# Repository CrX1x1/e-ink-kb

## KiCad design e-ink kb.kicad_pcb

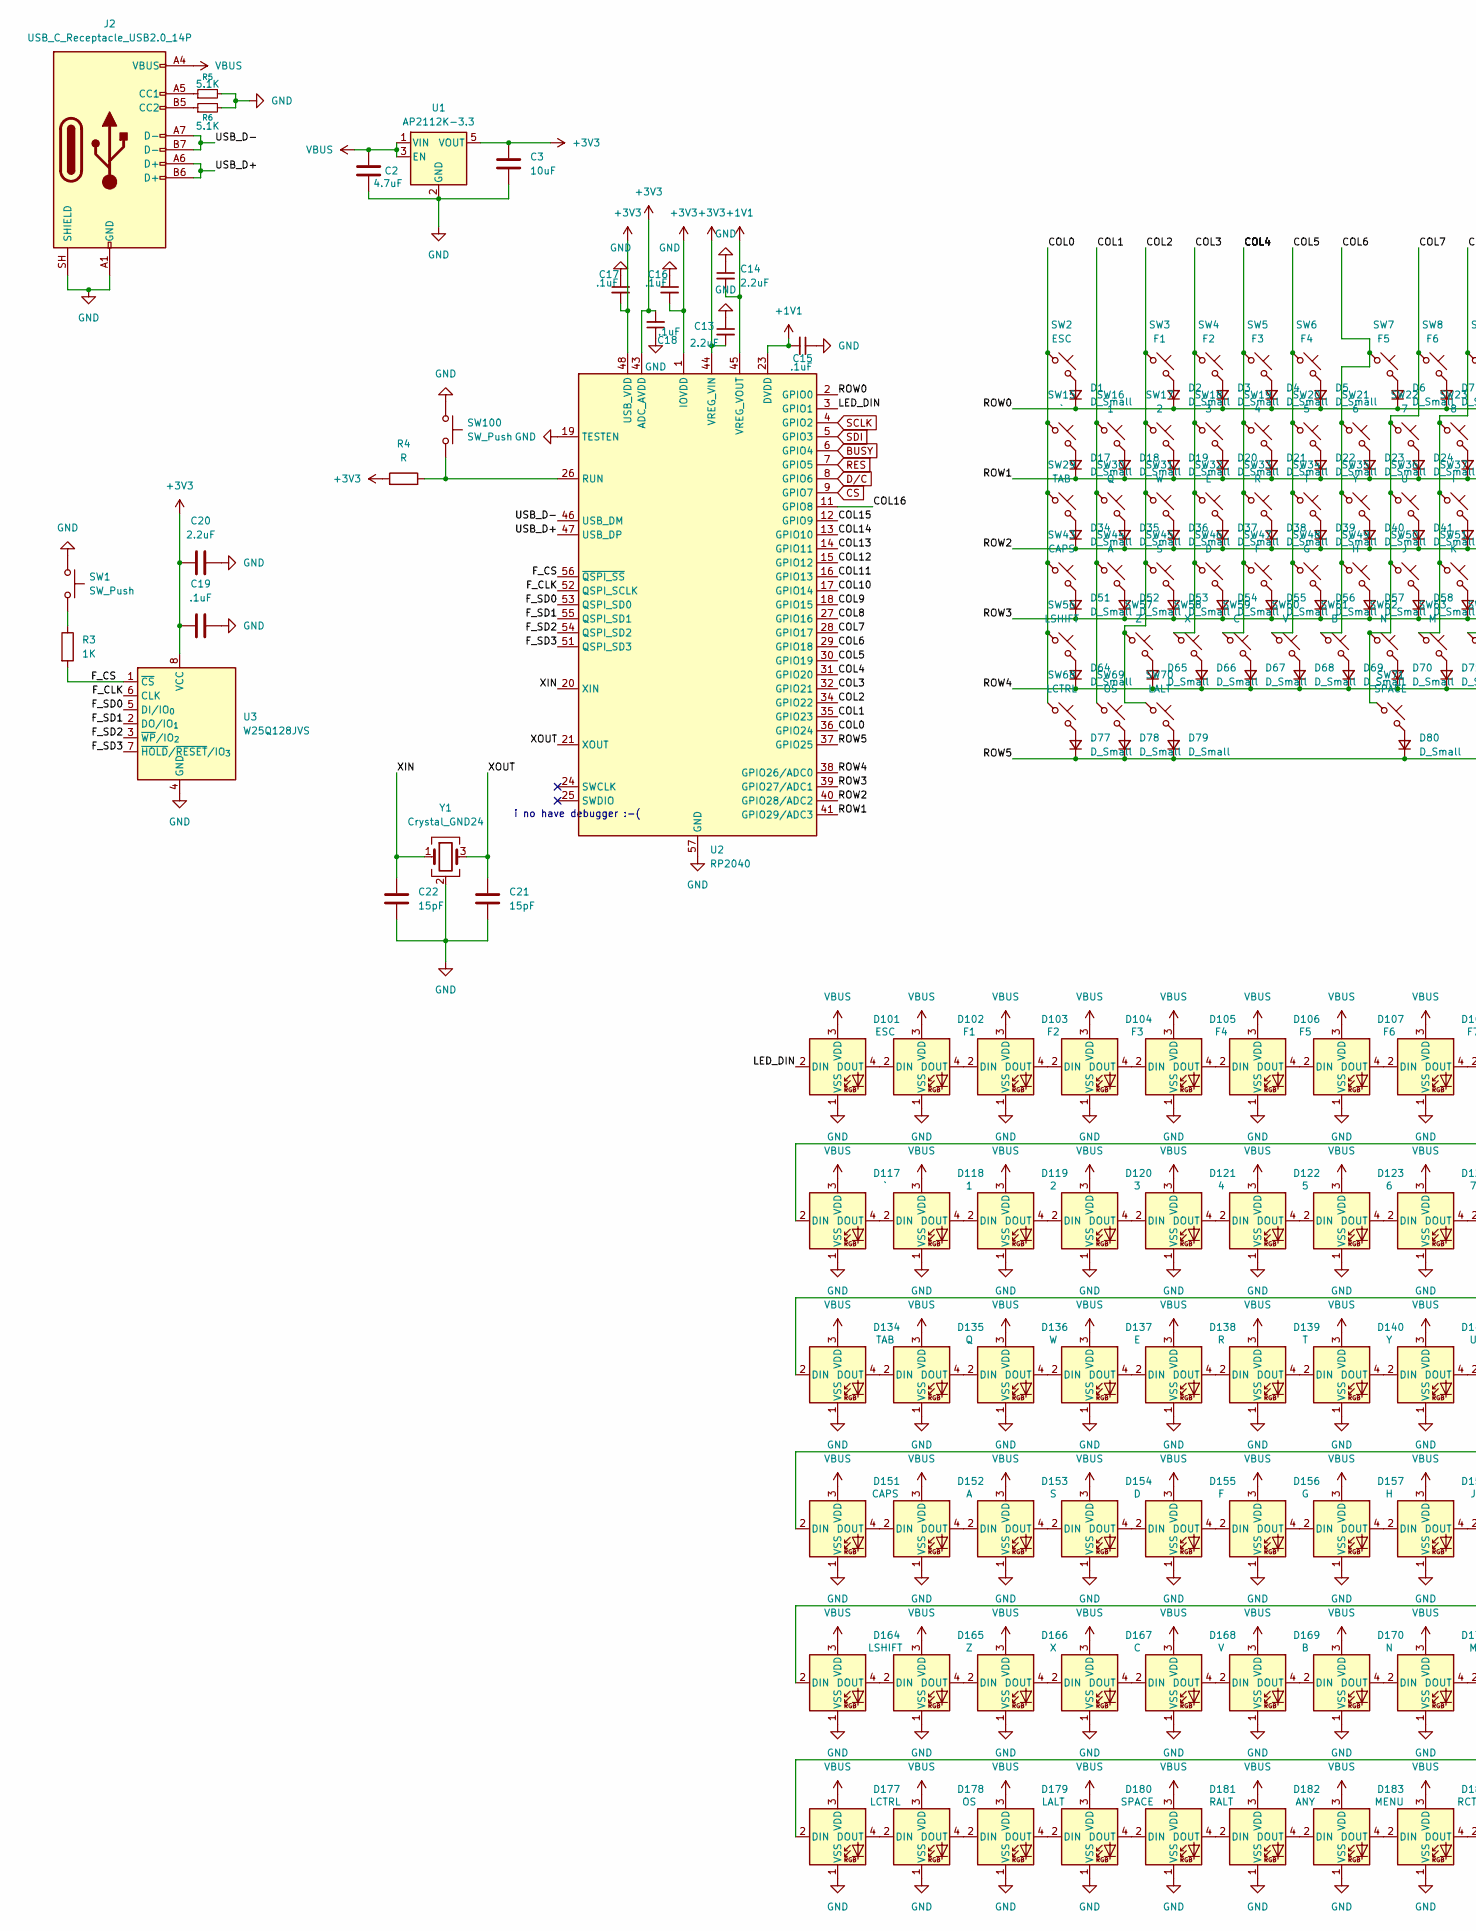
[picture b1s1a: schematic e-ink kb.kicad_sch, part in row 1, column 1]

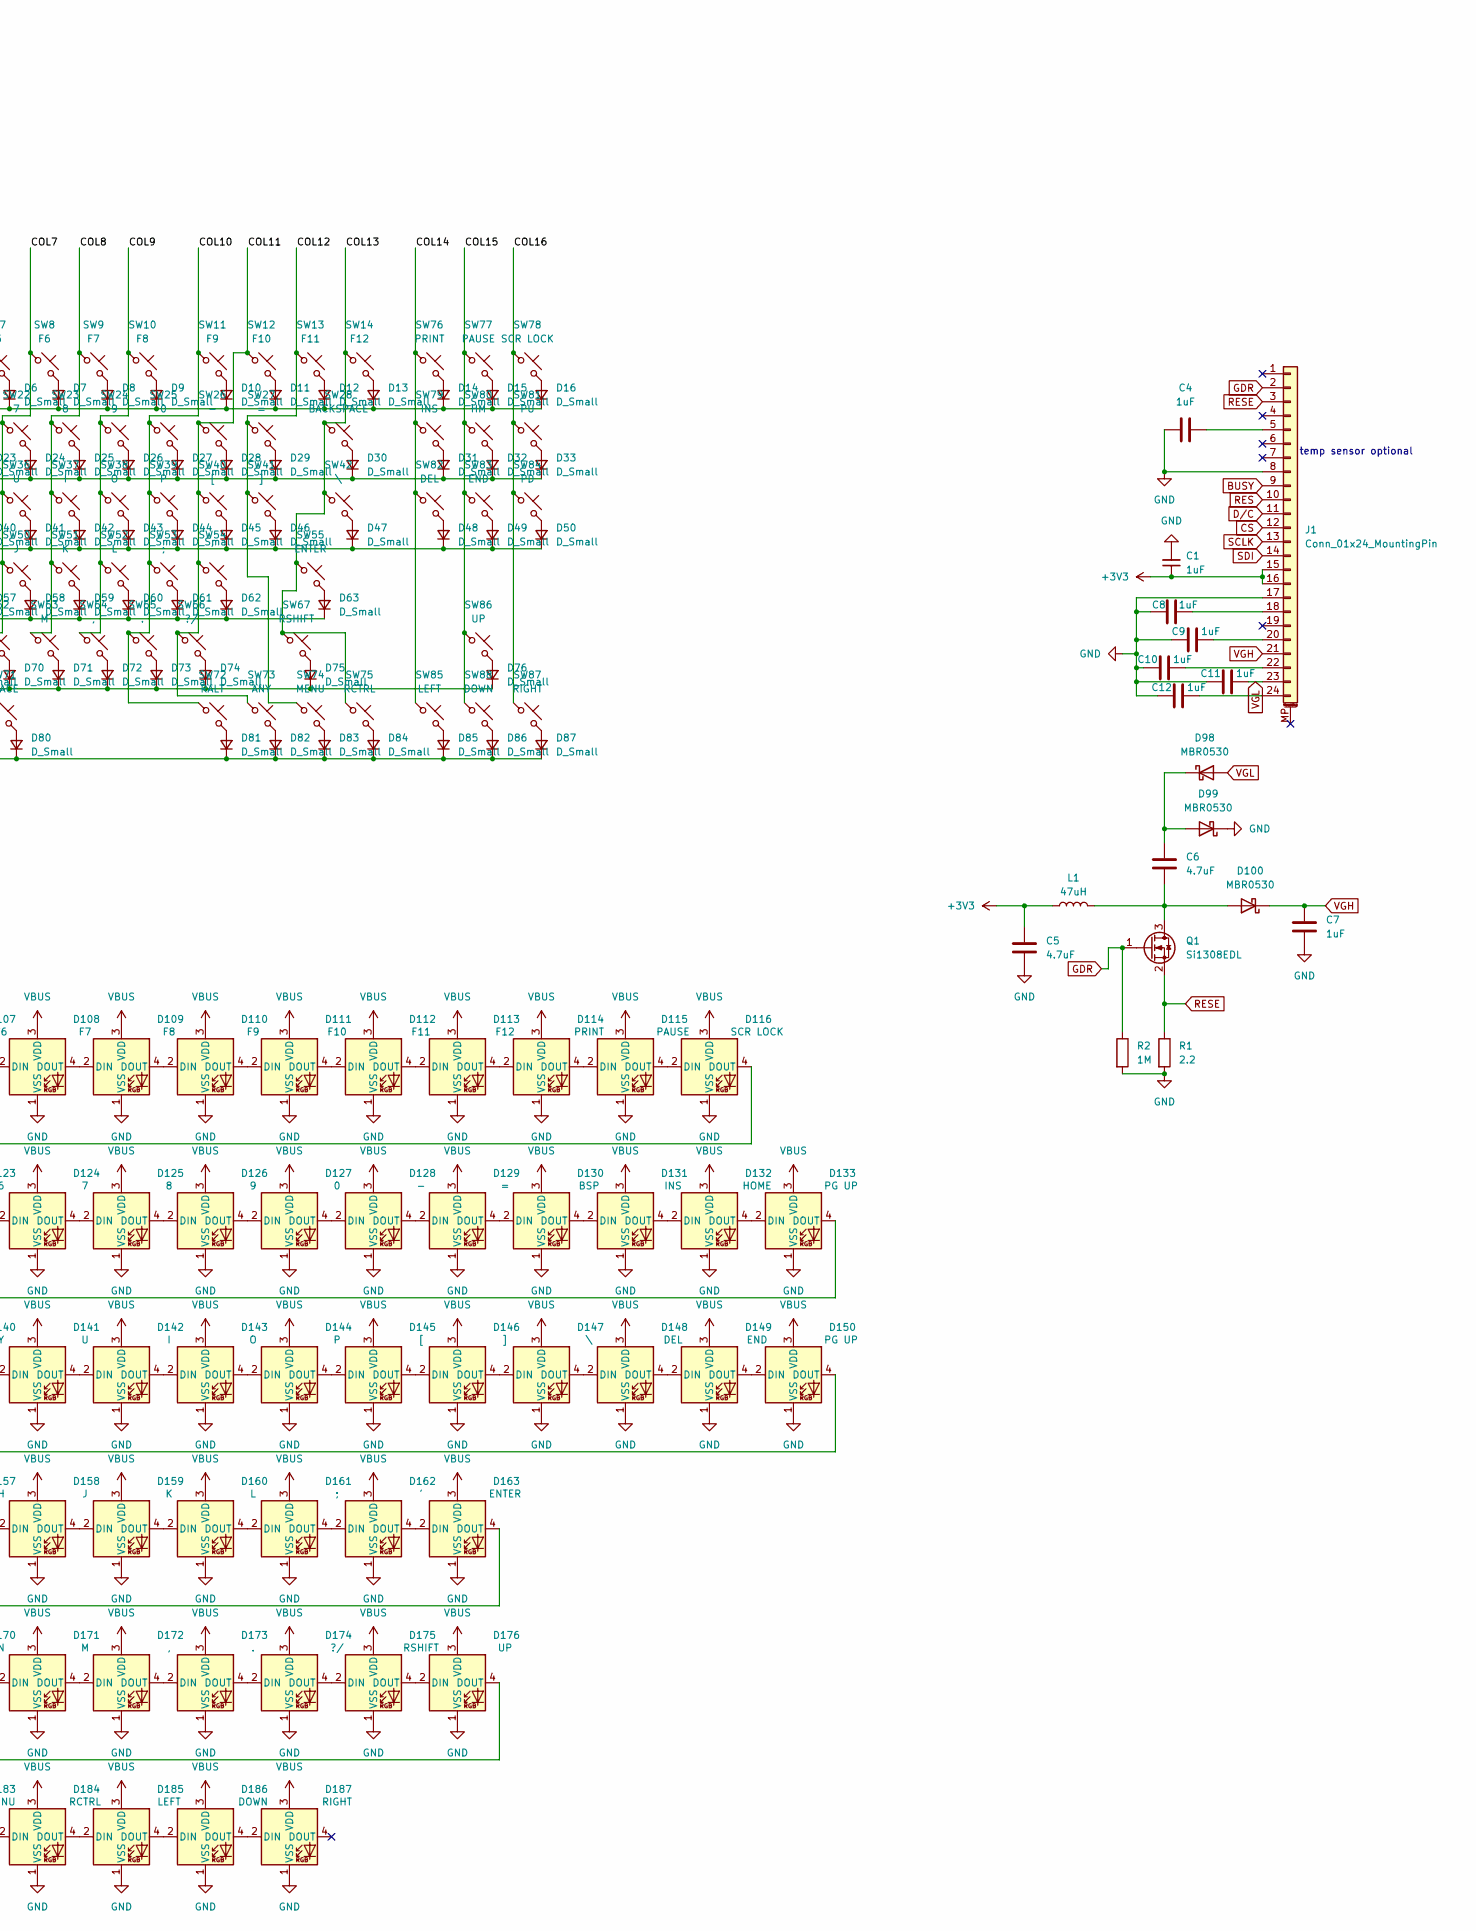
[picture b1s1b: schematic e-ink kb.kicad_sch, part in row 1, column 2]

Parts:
C1, C4, C7, C8, C9, C10, C11, C12: 1uF; C_0805_2012Metric_Pad1.18x1.45mm_HandSolder
C2, C5, C6: 4.7uF; C_0805_2012Metric_Pad1.18x1.45mm_HandSolder
C3: 10uF; C_0805_2012Metric_Pad1.18x1.45mm_HandSolder
C13, C14, C20: 2.2uF; C_0805_2012Metric_Pad1.18x1.45mm_HandSolder
C15, C16, C17, C18, C19: .1uF; C_0805_2012Metric_Pad1.18x1.45mm_HandSolder
C21, C22: 15pF; C_0805_2012Metric_Pad1.18x1.45mm_HandSolder
D1, D2, D3, D4, D5, D6, D7, D8, D9, D10, D11, D12, D13, D14, D15, D16, D17, D18, D19, D20, D21, D22, D23, D24, D25, D26, D27, D28, D29, D30, D31, D32, D33, D34, D35, D36, D37, D38, D39, D40, D41, D42, D43, D44, D45, D46, D47, D48, D49, D50, D51, D52, D53, D54, D55, D56, D57, D58, D59, D60, D61, D62, D63, D64, D65, D66, D67, D68, D69, D70, D71, D72, D73, D74, D75, D76, D77, D78, D79, D80, D81, D82, D83, D84, D85, D86, D87: D_Small; D_SOD-323F
D98, D99, D100: MBR0530; D_SOD-123
D101: ESC; LED_SK6812MINI-E_3.2x2.8mm_P1.5mm_ReverseMount
D102: F1; LED_SK6812MINI-E_3.2x2.8mm_P1.5mm_ReverseMount
D103: F2; LED_SK6812MINI-E_3.2x2.8mm_P1.5mm_ReverseMount
D104: F3; LED_SK6812MINI-E_3.2x2.8mm_P1.5mm_ReverseMount
D105: F4; LED_SK6812MINI-E_3.2x2.8mm_P1.5mm_ReverseMount
D106: F5; LED_SK6812MINI-E_3.2x2.8mm_P1.5mm_ReverseMount
D107: F6; LED_SK6812MINI-E_3.2x2.8mm_P1.5mm_ReverseMount
D108: F7; LED_SK6812MINI-E_3.2x2.8mm_P1.5mm_ReverseMount
D109: F8; LED_SK6812MINI-E_3.2x2.8mm_P1.5mm_ReverseMount
D110: F9; LED_SK6812MINI-E_3.2x2.8mm_P1.5mm_ReverseMount
D111: F10; LED_SK6812MINI-E_3.2x2.8mm_P1.5mm_ReverseMount
D112: F11; LED_SK6812MINI-E_3.2x2.8mm_P1.5mm_ReverseMount
D113: F12; LED_SK6812MINI-E_3.2x2.8mm_P1.5mm_ReverseMount
D114: PRINT; LED_SK6812MINI-E_3.2x2.8mm_P1.5mm_ReverseMount
D115: PAUSE; LED_SK6812MINI-E_3.2x2.8mm_P1.5mm_ReverseMount
D116: SCR LOCK; LED_SK6812MINI-E_3.2x2.8mm_P1.5mm_ReverseMount
D117: `; LED_SK6812MINI-E_3.2x2.8mm_P1.5mm_ReverseMount
D118: 1; LED_SK6812MINI-E_3.2x2.8mm_P1.5mm_ReverseMount
D119: 2; LED_SK6812MINI-E_3.2x2.8mm_P1.5mm_ReverseMount
D120: 3; LED_SK6812MINI-E_3.2x2.8mm_P1.5mm_ReverseMount
D121: 4; LED_SK6812MINI-E_3.2x2.8mm_P1.5mm_ReverseMount
D122: 5; LED_SK6812MINI-E_3.2x2.8mm_P1.5mm_ReverseMount
D123: 6; LED_SK6812MINI-E_3.2x2.8mm_P1.5mm_ReverseMount
D124: 7; LED_SK6812MINI-E_3.2x2.8mm_P1.5mm_ReverseMount
D125: 8; LED_SK6812MINI-E_3.2x2.8mm_P1.5mm_ReverseMount
D126: 9; LED_SK6812MINI-E_3.2x2.8mm_P1.5mm_ReverseMount
D127: 0; LED_SK6812MINI-E_3.2x2.8mm_P1.5mm_ReverseMount
D128: -; LED_SK6812MINI-E_3.2x2.8mm_P1.5mm_ReverseMount
D129: =; LED_SK6812MINI-E_3.2x2.8mm_P1.5mm_ReverseMount
D130: BSP; LED_SK6812MINI-E_3.2x2.8mm_P1.5mm_ReverseMount
D131: INS; LED_SK6812MINI-E_3.2x2.8mm_P1.5mm_ReverseMount
D132: HOME; LED_SK6812MINI-E_3.2x2.8mm_P1.5mm_ReverseMount
D133, D150: PG UP; LED_SK6812MINI-E_3.2x2.8mm_P1.5mm_ReverseMount
D134: TAB; LED_SK6812MINI-E_3.2x2.8mm_P1.5mm_ReverseMount
D135: Q; LED_SK6812MINI-E_3.2x2.8mm_P1.5mm_ReverseMount
D136: W; LED_SK6812MINI-E_3.2x2.8mm_P1.5mm_ReverseMount
D137: E; LED_SK6812MINI-E_3.2x2.8mm_P1.5mm_ReverseMount
D138: R; LED_SK6812MINI-E_3.2x2.8mm_P1.5mm_ReverseMount
D139: T; LED_SK6812MINI-E_3.2x2.8mm_P1.5mm_ReverseMount
D140: Y; LED_SK6812MINI-E_3.2x2.8mm_P1.5mm_ReverseMount
D141: U; LED_SK6812MINI-E_3.2x2.8mm_P1.5mm_ReverseMount
D142: I; LED_SK6812MINI-E_3.2x2.8mm_P1.5mm_ReverseMount
D143: O; LED_SK6812MINI-E_3.2x2.8mm_P1.5mm_ReverseMount
D144: P; LED_SK6812MINI-E_3.2x2.8mm_P1.5mm_ReverseMount
D145: [; LED_SK6812MINI-E_3.2x2.8mm_P1.5mm_ReverseMount
D146: ]; LED_SK6812MINI-E_3.2x2.8mm_P1.5mm_ReverseMount
D147: \; LED_SK6812MINI-E_3.2x2.8mm_P1.5mm_ReverseMount
D148: DEL; LED_SK6812MINI-E_3.2x2.8mm_P1.5mm_ReverseMount
D149: END; LED_SK6812MINI-E_3.2x2.8mm_P1.5mm_ReverseMount
D151: CAPS; LED_SK6812MINI-E_3.2x2.8mm_P1.5mm_ReverseMount
D152: A; LED_SK6812MINI-E_3.2x2.8mm_P1.5mm_ReverseMount
D153: S; LED_SK6812MINI-E_3.2x2.8mm_P1.5mm_ReverseMount
D154: D; LED_SK6812MINI-E_3.2x2.8mm_P1.5mm_ReverseMount
D155: F; LED_SK6812MINI-E_3.2x2.8mm_P1.5mm_ReverseMount
D156: G; LED_SK6812MINI-E_3.2x2.8mm_P1.5mm_ReverseMount
D157: H; LED_SK6812MINI-E_3.2x2.8mm_P1.5mm_ReverseMount
D158: J; LED_SK6812MINI-E_3.2x2.8mm_P1.5mm_ReverseMount
D159: K; LED_SK6812MINI-E_3.2x2.8mm_P1.5mm_ReverseMount
D160: L; LED_SK6812MINI-E_3.2x2.8mm_P1.5mm_ReverseMount
D161: ;; LED_SK6812MINI-E_3.2x2.8mm_P1.5mm_ReverseMount
D162: '; LED_SK6812MINI-E_3.2x2.8mm_P1.5mm_ReverseMount
D163: ENTER; LED_SK6812MINI-E_3.2x2.8mm_P1.5mm_ReverseMount
D164: LSHIFT; LED_SK6812MINI-E_3.2x2.8mm_P1.5mm_ReverseMount
D165: Z; LED_SK6812MINI-E_3.2x2.8mm_P1.5mm_ReverseMount
D166: X; LED_SK6812MINI-E_3.2x2.8mm_P1.5mm_ReverseMount
D167: C; LED_SK6812MINI-E_3.2x2.8mm_P1.5mm_ReverseMount
D168: V; LED_SK6812MINI-E_3.2x2.8mm_P1.5mm_ReverseMount
D169: B; LED_SK6812MINI-E_3.2x2.8mm_P1.5mm_ReverseMount
D170: N; LED_SK6812MINI-E_3.2x2.8mm_P1.5mm_ReverseMount
D171: M; LED_SK6812MINI-E_3.2x2.8mm_P1.5mm_ReverseMount
D172: ,; LED_SK6812MINI-E_3.2x2.8mm_P1.5mm_ReverseMount
D173: .; LED_SK6812MINI-E_3.2x2.8mm_P1.5mm_ReverseMount
D174: ?/; LED_SK6812MINI-E_3.2x2.8mm_P1.5mm_ReverseMount
D175: RSHIFT; LED_SK6812MINI-E_3.2x2.8mm_P1.5mm_ReverseMount
D176: UP; LED_SK6812MINI-E_3.2x2.8mm_P1.5mm_ReverseMount
D177: LCTRL; LED_SK6812MINI-E_3.2x2.8mm_P1.5mm_ReverseMount
D178: OS; LED_SK6812MINI-E_3.2x2.8mm_P1.5mm_ReverseMount
D179: LALT; LED_SK6812MINI-E_3.2x2.8mm_P1.5mm_ReverseMount
D180: SPACE; LED_SK6812MINI-E_3.2x2.8mm_P1.5mm_ReverseMount
D181: RALT; LED_SK6812MINI-E_3.2x2.8mm_P1.5mm_ReverseMount
D182: ANY; LED_SK6812MINI-E_3.2x2.8mm_P1.5mm_ReverseMount
D183: MENU; LED_SK6812MINI-E_3.2x2.8mm_P1.5mm_ReverseMount
D184: RCTRL; LED_SK6812MINI-E_3.2x2.8mm_P1.5mm_ReverseMount
D185: LEFT; LED_SK6812MINI-E_3.2x2.8mm_P1.5mm_ReverseMount
D186: DOWN; LED_SK6812MINI-E_3.2x2.8mm_P1.5mm_ReverseMount
D187: RIGHT; LED_SK6812MINI-E_3.2x2.8mm_P1.5mm_ReverseMount
J1: Conn_01x24_MountingPin; Molex_502231-2400_1x24-1SH_P0.5mm_Vertical
J2: USB_C_Receptacle_USB2.0_14P; USB_C_Receptacle_Amphenol_12401948E412A
L1: 47uH; L_APV_ANR3015
Q1: Si1308EDL; SOT-323_SC-70
R1: 2.2; R_0805_2012Metric_Pad1.20x1.40mm_HandSolder
R2: 1M; R_0805_2012Metric_Pad1.20x1.40mm_HandSolder
R3: 1K; R_0805_2012Metric_Pad1.20x1.40mm_HandSolder
R4: R; R_0805_2012Metric_Pad1.20x1.40mm_HandSolder
R5, R6: 5.1K; R_0805_2012Metric_Pad1.20x1.40mm_HandSolder
SW1, SW100: SW_Push; SW_Push_SPST_NO_Alps_SKRK
SW2: ESC; SW_Cherry_MX_1.00u_PCB
SW3: F1; SW_Cherry_MX_1.00u_PCB
SW4: F2; SW_Cherry_MX_1.00u_PCB
SW5: F3; SW_Cherry_MX_1.00u_PCB
SW6: F4; SW_Cherry_MX_1.00u_PCB
SW7: F5; SW_Cherry_MX_1.00u_PCB
SW8: F6; SW_Cherry_MX_1.00u_PCB
SW9: F7; SW_Cherry_MX_1.00u_PCB
SW10: F8; SW_Cherry_MX_1.00u_PCB
SW11: F9; SW_Cherry_MX_1.00u_PCB
SW12: F10; SW_Cherry_MX_1.00u_PCB
SW13: F11; SW_Cherry_MX_1.00u_PCB
SW14: F12; SW_Cherry_MX_1.00u_PCB
SW15: `; SW_Cherry_MX_1.00u_PCB
SW16: 1; SW_Cherry_MX_1.00u_PCB
SW17: 2; SW_Cherry_MX_1.00u_PCB
SW18: 3; SW_Cherry_MX_1.00u_PCB
SW19: 4; SW_Cherry_MX_1.00u_PCB
SW20: 5; SW_Cherry_MX_1.00u_PCB
SW21: 6; SW_Cherry_MX_1.00u_PCB
SW22: 7; SW_Cherry_MX_1.00u_PCB
SW23: 8; SW_Cherry_MX_1.00u_PCB
SW24: 9; SW_Cherry_MX_1.00u_PCB
SW25: 0; SW_Cherry_MX_1.00u_PCB
SW26: -; SW_Cherry_MX_1.00u_PCB
SW27: =; SW_Cherry_MX_1.00u_PCB
SW28: BACKSPACE; SW_Cherry_MX_2.00u_PCB
SW29: TAB; SW_Cherry_MX_1.50u_PCB
SW30: Q; SW_Cherry_MX_1.00u_PCB
SW31: W; SW_Cherry_MX_1.00u_PCB
SW32: E; SW_Cherry_MX_1.00u_PCB
SW33: R; SW_Cherry_MX_1.00u_PCB
SW34: T; SW_Cherry_MX_1.00u_PCB
SW35: Y; SW_Cherry_MX_1.00u_PCB
SW36: U; SW_Cherry_MX_1.00u_PCB
SW37: I; SW_Cherry_MX_1.00u_PCB
SW38: O; SW_Cherry_MX_1.00u_PCB
SW39: P; SW_Cherry_MX_1.00u_PCB
SW40: [; SW_Cherry_MX_1.00u_PCB
SW41: ]; SW_Cherry_MX_1.00u_PCB
SW42: \; SW_Cherry_MX_1.50u_PCB
SW43: CAPS; SW_Cherry_MX_1.75u_PCB
SW44: A; SW_Cherry_MX_1.00u_PCB
SW45: S; SW_Cherry_MX_1.00u_PCB
SW46: D; SW_Cherry_MX_1.00u_PCB
SW47: F; SW_Cherry_MX_1.00u_PCB
SW48: G; SW_Cherry_MX_1.00u_PCB
SW49: H; SW_Cherry_MX_1.00u_PCB
SW50: J; SW_Cherry_MX_1.00u_PCB
SW51: K; SW_Cherry_MX_1.00u_PCB
SW52: L; SW_Cherry_MX_1.00u_PCB
SW53: ;; SW_Cherry_MX_1.00u_PCB
SW54: '; SW_Cherry_MX_1.00u_PCB
SW55: ENTER; SW_Cherry_MX_2.25u_PCB
SW56: LSHIFT; SW_Cherry_MX_2.25u_PCB
SW57: Z; SW_Cherry_MX_1.00u_PCB
SW58: X; SW_Cherry_MX_1.00u_PCB
SW59: C; SW_Cherry_MX_1.00u_PCB
SW60: V; SW_Cherry_MX_1.00u_PCB
SW61: B; SW_Cherry_MX_1.00u_PCB
SW62: N; SW_Cherry_MX_1.00u_PCB
SW63: M; SW_Cherry_MX_1.00u_PCB
SW64: ,; SW_Cherry_MX_1.00u_PCB
SW65: .; SW_Cherry_MX_1.00u_PCB
SW66: ?/; SW_Cherry_MX_1.00u_PCB
SW67: RSHIFT; SW_Cherry_MX_2.75u_PCB
SW68: LCTRL; SW_Cherry_MX_1.25u_PCB
SW69: OS; SW_Cherry_MX_1.25u_PCB
SW70: LALT; SW_Cherry_MX_1.25u_PCB
SW71: SPACE; SW_Cherry_MX_6.25u_PCB
SW72: RALT; SW_Cherry_MX_1.25u_PCB
SW73: ANY; SW_Cherry_MX_1.25u_PCB
SW74: MENU; SW_Cherry_MX_1.25u_PCB
SW75: RCTRL; SW_Cherry_MX_1.25u_PCB
SW76: PRINT; SW_Cherry_MX_1.00u_PCB
SW77: PAUSE; SW_Cherry_MX_1.00u_PCB
SW78: SCR LOCK; SW_Cherry_MX_1.00u_PCB
SW79: INS; SW_Cherry_MX_1.00u_PCB
SW80: HM; SW_Cherry_MX_1.00u_PCB
SW81: PU; SW_Cherry_MX_1.00u_PCB
SW82: DEL; SW_Cherry_MX_1.00u_PCB
SW83: END; SW_Cherry_MX_1.00u_PCB
SW84: PD; SW_Cherry_MX_1.00u_PCB
SW85: LEFT; SW_Cherry_MX_1.00u_PCB
SW86: UP; SW_Cherry_MX_1.00u_PCB
SW87: RIGHT; SW_Cherry_MX_1.00u_PCB
SW88: DOWN; SW_Cherry_MX_1.00u_PCB
U1: AP2112K-3.3; SOT-23-5
U2: RP2040; QFN-56-1EP_7x7mm_P0.4mm_EP3.2x3.2mm
U3: W25Q128JVS; SOIC-8_5.3x5.3mm_P1.27mm
Y1: Crystal_GND24; Crystal_SMD_3225-4Pin_3.2x2.5mm_HandSoldering

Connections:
+1V1: C14.2, C15.2, U2.23 (DVDD), U2.45 (VREG_VOUT), U2.50 (DVDD)
+3V3: C1.1, C3.1, C5.1, C13.2, C16.2, C17.2, C18.2, C19.2, C20.2, J1.15, J1.16, L1.1, R4.1, U1.5 (VOUT), U2.1 (IOVDD), U2.10 (IOVDD), U2.22 (IOVDD), U2.33 (IOVDD), U2.42 (IOVDD), U2.43 (ADC_AVDD), U2.44 (VREG_VIN), U2.48 (USB_VDD), U2.49 (IOVDD), U3.8 (VCC)
/COL0: SW2.1, SW15.1, SW29.1, SW43.1, SW56.1, SW68.1, U2.36 (GPIO24)
/COL1: SW16.1, SW30.1, SW44.1, SW69.1, U2.35 (GPIO23)
/COL2: SW3.1, SW17.1, SW31.1, SW45.1, SW57.1, SW70.1, U2.34 (GPIO22)
/COL3: SW4.1, SW18.1, SW32.1, SW46.1, SW58.1, U2.32 (GPIO21)
/COL4: SW5.1, SW19.1, SW33.1, SW47.1, SW59.1, U2.31 (GPIO20)
/COL5: SW6.1, SW20.1, SW34.1, SW48.1, SW60.1, U2.30 (GPIO19)
/COL6: SW7.1, SW21.1, SW35.1, SW49.1, SW61.1, U2.29 (GPIO18)
/COL7: SW8.1, SW22.1, SW36.1, SW50.1, SW62.1, SW71.1, U2.28 (GPIO17)
/COL8: SW9.1, SW23.1, SW37.1, SW51.1, SW63.1, U2.27 (GPIO16)
/COL9: SW10.1, SW24.1, SW38.1, SW52.1, SW64.1, U2.18 (GPIO15)
/COL10: SW11.1, SW25.1, SW39.1, SW53.1, SW65.1, SW72.1, U2.17 (GPIO14)
/COL11: SW12.1, SW26.1, SW40.1, SW54.1, SW66.1, SW73.1, U2.16 (GPIO13)
/COL12: SW13.1, SW27.1, SW41.1, SW74.1, U2.15 (GPIO12)
/COL13: SW14.1, SW28.1, SW42.1, SW55.1, SW67.1, SW75.1, U2.14 (GPIO11)
/COL14: SW76.1, SW79.1, SW82.1, SW85.1, U2.13 (GPIO10)
/COL15: SW77.1, SW80.1, SW83.1, SW86.1, SW88.1, U2.12 (GPIO9)
/COL16: SW78.1, SW81.1, SW84.1, SW87.1, U2.11 (GPIO8)
/F_CLK: U2.52 (QSPI_SCLK), U3.6 (CLK)
/F_CS: R3.2, U2.56 (~QSPI_SS), U3.1 (~CS)
/F_SD0: U2.53 (QSPI_SD0), U3.5 (DI/IO_{0})
/F_SD1: U2.55 (QSPI_SD1), U3.2 (DO/IO_{1})
/F_SD2: U2.54 (QSPI_SD2), U3.3 (~WP/IO_{2})
/F_SD3: U2.51 (QSPI_SD3), U3.7 (~HOLD/~RESET/IO_{3})
/LED_DIN: D101.2 (DIN), U2.3 (GPIO1)
/ROW0: D1.1 (K), D2.1 (K), D3.1 (K), D4.1 (K), D5.1 (K), D6.1 (K), D7.1 (K), D8.1 (K), D9.1 (K), D10.1 (K), D11.1 (K), D12.1 (K), D13.1 (K), D14.1 (K), D15.1 (K), D16.1 (K), U2.2 (GPIO0)
/ROW1: D17.1 (K), D18.1 (K), D19.1 (K), D20.1 (K), D21.1 (K), D22.1 (K), D23.1 (K), D24.1 (K), D25.1 (K), D26.1 (K), D27.1 (K), D28.1 (K), D29.1 (K), D30.1 (K), D31.1 (K), D32.1 (K), D33.1 (K), U2.41 (GPIO29/ADC3)
/ROW2: D34.1 (K), D35.1 (K), D36.1 (K), D37.1 (K), D38.1 (K), D39.1 (K), D40.1 (K), D41.1 (K), D42.1 (K), D43.1 (K), D44.1 (K), D45.1 (K), D46.1 (K), D47.1 (K), D48.1 (K), D49.1 (K), D50.1 (K), U2.40 (GPIO28/ADC2)
/ROW3: D51.1 (K), D52.1 (K), D53.1 (K), D54.1 (K), D55.1 (K), D56.1 (K), D57.1 (K), D58.1 (K), D59.1 (K), D60.1 (K), D61.1 (K), D62.1 (K), D63.1 (K), U2.39 (GPIO27/ADC1)
/ROW4: D64.1 (K), D65.1 (K), D66.1 (K), D67.1 (K), D68.1 (K), D69.1 (K), D70.1 (K), D71.1 (K), D72.1 (K), D73.1 (K), D74.1 (K), D75.1 (K), D76.1 (K), U2.38 (GPIO26/ADC0)
/ROW5: D77.1 (K), D78.1 (K), D79.1 (K), D80.1 (K), D81.1 (K), D82.1 (K), D83.1 (K), D84.1 (K), D85.1 (K), D86.1 (K), D87.1 (K), U2.37 (GPIO25)
/USB_D+: J2.A6 (D+), J2.B6 (D+), U2.47 (USB_DP)
/USB_D-: J2.A7 (D-), J2.B7 (D-), U2.46 (USB_DM)
/XIN: C22.1, U2.20 (XIN), Y1.1
/XOUT: C21.1, U2.21 (XOUT), Y1.3
BUSY: J1.9, U2.6 (GPIO4)
CS: J1.12, U2.9 (GPIO7)
D/C: J1.11, U2.8 (GPIO6)
GDR: J1.2, Q1.1 (G), R2.1
GND: C1.2, C2.2, C3.2, C4.1, C5.2, C7.2, C8.1, C9.1, C10.1, C11.1, C12.1, C13.1, C14.1, C15.1, C16.1, C17.1, C18.1, C19.1, C20.1, C21.2, C22.2, D99.1 (K), D101.1 (VSS), D102.1 (VSS), D103.1 (VSS), D104.1 (VSS), D105.1 (VSS), D106.1 (VSS), D107.1 (VSS), D108.1 (VSS), D109.1 (VSS), D110.1 (VSS), D111.1 (VSS), D112.1 (VSS), D113.1 (VSS), D114.1 (VSS), D115.1 (VSS), D116.1 (VSS), D117.1 (VSS), D118.1 (VSS), D119.1 (VSS), D120.1 (VSS), D121.1 (VSS), D122.1 (VSS), D123.1 (VSS), D124.1 (VSS), D125.1 (VSS), D126.1 (VSS), D127.1 (VSS), D128.1 (VSS), D129.1 (VSS), D130.1 (VSS), D131.1 (VSS), D132.1 (VSS), D133.1 (VSS), D134.1 (VSS), D135.1 (VSS), D136.1 (VSS), D137.1 (VSS), D138.1 (VSS), D139.1 (VSS), D140.1 (VSS), D141.1 (VSS), D142.1 (VSS), D143.1 (VSS), D144.1 (VSS), D145.1 (VSS), D146.1 (VSS), D147.1 (VSS), D148.1 (VSS), D149.1 (VSS), D150.1 (VSS), D151.1 (VSS), D152.1 (VSS), D153.1 (VSS), D154.1 (VSS), D155.1 (VSS), D156.1 (VSS), D157.1 (VSS), D158.1 (VSS), D159.1 (VSS), D160.1 (VSS), D161.1 (VSS), D162.1 (VSS), D163.1 (VSS), D164.1 (VSS), D165.1 (VSS), D166.1 (VSS), D167.1 (VSS), D168.1 (VSS), D169.1 (VSS), D170.1 (VSS), D171.1 (VSS), D172.1 (VSS), D173.1 (VSS), D174.1 (VSS), D175.1 (VSS), D176.1 (VSS), D177.1 (VSS), D178.1 (VSS), D179.1 (VSS), D180.1 (VSS), D181.1 (VSS), D182.1 (VSS), D183.1 (VSS), D184.1 (VSS), D185.1 (VSS), D186.1 (VSS), D187.1 (VSS), J1.8, J1.17, J2.A1 (GND), J2.A12 (GND), J2.B1 (GND), J2.B12 (GND), J2.SH (SHIELD), R1.2, R2.2, R5.2, R6.2, SW1.1, SW100.1, U1.2 (GND), U2.19 (TESTEN), U2.57 (GND), U3.4 (GND), Y1.2 (G), Y1.4 (G)
unnamed: D1.2 (A), SW2.2
unnamed: D2.2 (A), SW3.2
unnamed: D3.2 (A), SW4.2
unnamed: D4.2 (A), SW5.2
unnamed: D5.2 (A), SW6.2
unnamed: D6.2 (A), SW7.2
unnamed: D7.2 (A), SW8.2
unnamed: D8.2 (A), SW9.2
unnamed: D9.2 (A), SW10.2
unnamed: D10.2 (A), SW11.2
unnamed: D11.2 (A), SW12.2
unnamed: D12.2 (A), SW13.2
unnamed: D13.2 (A), SW14.2
unnamed: D14.2 (A), SW76.2
unnamed: D15.2 (A), SW77.2
unnamed: D16.2 (A), SW78.2
unnamed: D17.2 (A), SW15.2
unnamed: D18.2 (A), SW16.2
unnamed: D19.2 (A), SW17.2
unnamed: D20.2 (A), SW18.2
unnamed: D21.2 (A), SW19.2
unnamed: D22.2 (A), SW20.2
unnamed: D23.2 (A), SW21.2
unnamed: D24.2 (A), SW22.2
unnamed: D25.2 (A), SW23.2
unnamed: D26.2 (A), SW24.2
unnamed: D27.2 (A), SW25.2
unnamed: D28.2 (A), SW26.2
unnamed: D29.2 (A), SW27.2
unnamed: D30.2 (A), SW28.2
unnamed: D31.2 (A), SW79.2
unnamed: D32.2 (A), SW80.2
unnamed: D33.2 (A), SW81.2
unnamed: D34.2 (A), SW29.2
unnamed: D35.2 (A), SW30.2
unnamed: D36.2 (A), SW31.2
unnamed: D37.2 (A), SW32.2
unnamed: D38.2 (A), SW33.2
unnamed: D39.2 (A), SW34.2
unnamed: D40.2 (A), SW35.2
unnamed: D41.2 (A), SW36.2
unnamed: D42.2 (A), SW37.2
unnamed: D43.2 (A), SW38.2
unnamed: D44.2 (A), SW39.2
unnamed: D45.2 (A), SW40.2
unnamed: D46.2 (A), SW41.2
unnamed: D47.2 (A), SW42.2
unnamed: D48.2 (A), SW82.2
unnamed: D49.2 (A), SW83.2
unnamed: D50.2 (A), SW84.2
unnamed: D51.2 (A), SW43.2
unnamed: D52.2 (A), SW44.2
unnamed: D53.2 (A), SW45.2
unnamed: D54.2 (A), SW46.2
unnamed: D55.2 (A), SW47.2
unnamed: D56.2 (A), SW48.2
unnamed: D57.2 (A), SW49.2
unnamed: D58.2 (A), SW50.2
unnamed: D59.2 (A), SW51.2
unnamed: D60.2 (A), SW52.2
unnamed: D61.2 (A), SW53.2
unnamed: D62.2 (A), SW54.2
unnamed: D63.2 (A), SW55.2
unnamed: D64.2 (A), SW56.2
unnamed: D65.2 (A), SW57.2
unnamed: D66.2 (A), SW58.2
unnamed: D67.2 (A), SW59.2
unnamed: D68.2 (A), SW60.2
unnamed: D69.2 (A), SW61.2
unnamed: D70.2 (A), SW62.2
unnamed: D71.2 (A), SW63.2
unnamed: D72.2 (A), SW64.2
unnamed: D73.2 (A), SW65.2
unnamed: D74.2 (A), SW66.2
unnamed: D75.2 (A), SW67.2
unnamed: D76.2 (A), SW86.2
unnamed: D77.2 (A), SW68.2
unnamed: D78.2 (A), SW69.2
unnamed: D79.2 (A), SW70.2
unnamed: D80.2 (A), SW71.2
unnamed: D81.2 (A), SW72.2
unnamed: D82.2 (A), SW73.2
unnamed: D83.2 (A), SW74.2
unnamed: D84.2 (A), SW75.2
unnamed: D85.2 (A), SW85.2
unnamed: D86.2 (A), SW88.2
unnamed: D87.2 (A), SW87.2
unnamed: C6.1, D98.1 (K), D99.2 (A)
unnamed: C6.2, D100.2 (A), L1.2, Q1.3 (D)
unnamed: D101.4 (DOUT), D102.2 (DIN)
unnamed: D102.4 (DOUT), D103.2 (DIN)
unnamed: D103.4 (DOUT), D104.2 (DIN)
unnamed: D104.4 (DOUT), D105.2 (DIN)
unnamed: D105.4 (DOUT), D106.2 (DIN)
unnamed: D106.4 (DOUT), D107.2 (DIN)
unnamed: D107.4 (DOUT), D108.2 (DIN)
unnamed: D108.4 (DOUT), D109.2 (DIN)
unnamed: D109.4 (DOUT), D110.2 (DIN)
unnamed: D110.4 (DOUT), D111.2 (DIN)
unnamed: D111.4 (DOUT), D112.2 (DIN)
unnamed: D112.4 (DOUT), D113.2 (DIN)
unnamed: D113.4 (DOUT), D114.2 (DIN)
unnamed: D114.4 (DOUT), D115.2 (DIN)
unnamed: D115.4 (DOUT), D116.2 (DIN)
unnamed: D116.4 (DOUT), D117.2 (DIN)
unnamed: D117.4 (DOUT), D118.2 (DIN)
unnamed: D118.4 (DOUT), D119.2 (DIN)
unnamed: D119.4 (DOUT), D120.2 (DIN)
unnamed: D120.4 (DOUT), D121.2 (DIN)
unnamed: D121.4 (DOUT), D122.2 (DIN)
unnamed: D122.4 (DOUT), D123.2 (DIN)
unnamed: D123.4 (DOUT), D124.2 (DIN)
unnamed: D124.4 (DOUT), D125.2 (DIN)
unnamed: D125.4 (DOUT), D126.2 (DIN)
unnamed: D126.4 (DOUT), D127.2 (DIN)
unnamed: D127.4 (DOUT), D128.2 (DIN)
unnamed: D128.4 (DOUT), D129.2 (DIN)
unnamed: D129.4 (DOUT), D130.2 (DIN)
unnamed: D130.4 (DOUT), D131.2 (DIN)
unnamed: D131.4 (DOUT), D132.2 (DIN)
unnamed: D132.4 (DOUT), D133.2 (DIN)
unnamed: D133.4 (DOUT), D134.2 (DIN)
unnamed: D134.4 (DOUT), D135.2 (DIN)
unnamed: D135.4 (DOUT), D136.2 (DIN)
unnamed: D136.4 (DOUT), D137.2 (DIN)
unnamed: D137.4 (DOUT), D138.2 (DIN)
unnamed: D138.4 (DOUT), D139.2 (DIN)
unnamed: D139.4 (DOUT), D140.2 (DIN)
unnamed: D140.4 (DOUT), D141.2 (DIN)
unnamed: D141.4 (DOUT), D142.2 (DIN)
unnamed: D142.4 (DOUT), D143.2 (DIN)
unnamed: D143.4 (DOUT), D144.2 (DIN)
unnamed: D144.4 (DOUT), D145.2 (DIN)
unnamed: D145.4 (DOUT), D146.2 (DIN)
unnamed: D146.4 (DOUT), D147.2 (DIN)
unnamed: D147.4 (DOUT), D148.2 (DIN)
unnamed: D148.4 (DOUT), D149.2 (DIN)
unnamed: D149.4 (DOUT), D150.2 (DIN)
unnamed: D150.4 (DOUT), D151.2 (DIN)
unnamed: D151.4 (DOUT), D152.2 (DIN)
unnamed: D152.4 (DOUT), D153.2 (DIN)
unnamed: D153.4 (DOUT), D154.2 (DIN)
unnamed: D154.4 (DOUT), D155.2 (DIN)
unnamed: D155.4 (DOUT), D156.2 (DIN)
unnamed: D156.4 (DOUT), D157.2 (DIN)
unnamed: D157.4 (DOUT), D158.2 (DIN)
unnamed: D158.4 (DOUT), D159.2 (DIN)
unnamed: D159.4 (DOUT), D160.2 (DIN)
unnamed: D160.4 (DOUT), D161.2 (DIN)
unnamed: D161.4 (DOUT), D162.2 (DIN)
unnamed: D162.4 (DOUT), D163.2 (DIN)
unnamed: D163.4 (DOUT), D164.2 (DIN)
unnamed: D164.4 (DOUT), D165.2 (DIN)
unnamed: D165.4 (DOUT), D166.2 (DIN)
unnamed: D166.4 (DOUT), D167.2 (DIN)
unnamed: D167.4 (DOUT), D168.2 (DIN)
unnamed: D168.4 (DOUT), D169.2 (DIN)
unnamed: D169.4 (DOUT), D170.2 (DIN)
unnamed: D170.4 (DOUT), D171.2 (DIN)
unnamed: D171.4 (DOUT), D172.2 (DIN)
unnamed: D172.4 (DOUT), D173.2 (DIN)
unnamed: D173.4 (DOUT), D174.2 (DIN)
unnamed: D174.4 (DOUT), D175.2 (DIN)
unnamed: D175.4 (DOUT), D176.2 (DIN)
unnamed: D176.4 (DOUT), D177.2 (DIN)
unnamed: D177.4 (DOUT), D178.2 (DIN)
unnamed: D178.4 (DOUT), D179.2 (DIN)
unnamed: D179.4 (DOUT), D180.2 (DIN)
unnamed: D180.4 (DOUT), D181.2 (DIN)
unnamed: D181.4 (DOUT), D182.2 (DIN)
unnamed: D182.4 (DOUT), D183.2 (DIN)
unnamed: D183.4 (DOUT), D184.2 (DIN)
unnamed: D184.4 (DOUT), D185.2 (DIN)
unnamed: D185.4 (DOUT), D186.2 (DIN)
unnamed: D186.4 (DOUT), D187.2 (DIN)
unnamed: C4.2, J1.5
unnamed: C8.2, J1.18
unnamed: C9.2, J1.20
unnamed: C10.2, J1.22
unnamed: C12.2, J1.24
unnamed: J2.A5 (CC1), R5.1
unnamed: J2.B5 (CC2), R6.1
unnamed: R3.1, SW1.2
unnamed: R4.2, SW100.2, U2.26 (RUN)
RES: J1.10, U2.7 (GPIO5)
RESE: J1.3, Q1.2 (S), R1.1
SCLK: J1.13, U2.4 (GPIO2)
SDI: J1.14, U2.5 (GPIO3)
VBUS: C2.1, D101.3 (VDD), D102.3 (VDD), D103.3 (VDD), D104.3 (VDD), D105.3 (VDD), D106.3 (VDD), D107.3 (VDD), D108.3 (VDD), D109.3 (VDD), D110.3 (VDD), D111.3 (VDD), D112.3 (VDD), D113.3 (VDD), D114.3 (VDD), D115.3 (VDD), D116.3 (VDD), D117.3 (VDD), D118.3 (VDD), D119.3 (VDD), D120.3 (VDD), D121.3 (VDD), D122.3 (VDD), D123.3 (VDD), D124.3 (VDD), D125.3 (VDD), D126.3 (VDD), D127.3 (VDD), D128.3 (VDD), D129.3 (VDD), D130.3 (VDD), D131.3 (VDD), D132.3 (VDD), D133.3 (VDD), D134.3 (VDD), D135.3 (VDD), D136.3 (VDD), D137.3 (VDD), D138.3 (VDD), D139.3 (VDD), D140.3 (VDD), D141.3 (VDD), D142.3 (VDD), D143.3 (VDD), D144.3 (VDD), D145.3 (VDD), D146.3 (VDD), D147.3 (VDD), D148.3 (VDD), D149.3 (VDD), D150.3 (VDD), D151.3 (VDD), D152.3 (VDD), D153.3 (VDD), D154.3 (VDD), D155.3 (VDD), D156.3 (VDD), D157.3 (VDD), D158.3 (VDD), D159.3 (VDD), D160.3 (VDD), D161.3 (VDD), D162.3 (VDD), D163.3 (VDD), D164.3 (VDD), D165.3 (VDD), D166.3 (VDD), D167.3 (VDD), D168.3 (VDD), D169.3 (VDD), D170.3 (VDD), D171.3 (VDD), D172.3 (VDD), D173.3 (VDD), D174.3 (VDD), D175.3 (VDD), D176.3 (VDD), D177.3 (VDD), D178.3 (VDD), D179.3 (VDD), D180.3 (VDD), D181.3 (VDD), D182.3 (VDD), D183.3 (VDD), D184.3 (VDD), D185.3 (VDD), D186.3 (VDD), D187.3 (VDD), J2.A4 (VBUS), J2.A9 (VBUS), J2.B4 (VBUS), J2.B9 (VBUS), U1.1 (VIN), U1.3 (EN)
VGH: C7.1, D100.1 (K), J1.21
VGL: C11.2, D98.2 (A), J1.23

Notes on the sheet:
temp sensor optional
i no have debugger :-(

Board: 2 copper layers, 302 parts (215 on the bottom side), 232 nets, no tracks yet.
